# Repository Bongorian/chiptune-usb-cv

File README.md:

# Chiptune USB/CV

SAA1099 × 1、SN76489AN × 2、RP2040を搭載したPSG音源のハードウェア・ファームウェアプロジェクトです。
USB MIDI、TRS MIDI、2系統のCV／ゲート入力と、OLED・3ボタンによる操作を想定しています。
回路図、配線済みPCB、JLCPCB向け製造データ、設計資料を収録しています。

ファームウェアはv0.11.0-alphaです。初期配置はMIDI 10（ch1–6: SAA、ch7–9: 左右SNトーン、ch10: 左右SNノイズ）。DIRECT/POLY演奏、PAN/CC10、音色編集、Patch/Track/Project/System保存に対応します。[操作資料](firmware/README.md)と[音源構成](firmware/SOUND_DESIGN.md)を参照してください。

SN共通クロックはHz／PIO値で設定でき、RAW／BASE／FULL、2スロットFX、計算周波数と転送待ちの診断に対応します。[クロック仕様と実機未確認事項](firmware/SN_CLOCK.md)を参照してください。

保存形式はversion 11、Web MIDI通信はprotocol 3/schema 11です。旧形式の音色・CV校正・明るさは移行しません。起動時のフラッシュ消去・書き込みは行いません。

自動テスト・ARMビルド・UF2検証の結果は[検証記録](firmware/dist/Test_Verification.json)に記録しています。実機の音声出力、電気特性、1 ms更新の最悪実行時間は未検証です。[検証範囲](firmware/ARCHITECTURE.md)と[実機確認項目](firmware/BRINGUP.md)を参照してください。

[**Wave Lab — Web MIDI音色エディタ**](https://bongorian.github.io/chiptune-usb-cv/)

Wave Labのソースは`editor/`にあります。公開版のほか、ローカルHTTPサーバーでも実行できます。[音作り](firmware/SOUND_DESIGN.md)と[エディタの使い方](editor/README.md)を参照してください。

## 仕様

| 項目 | 内容 |
|---|---|
| 基板 | 85 × 54 mm、4層、FR-4 1.6 mm、角R3、M2用取り付け穴 |
| マイコン | RP2040、外部QSPIフラッシュ |
| 音源 | SAA1099 DIP18 × 1、SN76489AN DIP16 × 2 |
| 電源 | USB-C給電 |
| MIDI | USB MIDIデバイス、3.5 mm TRS Type A入力 |
| CV | 1 V/oct入力 × 2、系統別の2点校正を想定 |
| ゲート | 0–5 V／0–10 V入力 × 2 |
| オーディオ | 3.5 mmステレオライン出力、入力インピーダンス10 kΩ以上の外部アンプ向け |
| 操作 | 0.96インチ128 × 64 OLED、3ボタン |

## リポジトリ構成

| ディレクトリ | 内容 |
|---|---|
| `routed/` | 配線済みKiCadプロジェクト、シンボル、フットプリント |
| `hardware/` | 回路・配置生成用の未配線プロジェクト |
| `editor/` | GitHub Pages向けWeb MIDI音色エディタ、波形・ADSR・16ステップ・クロック・CV設定 |
| `firmware/` | RP2040音源エンジン、USB／TRS MIDI、CV／ゲート、OLED UI、プリセット、UF2 |
| `mechanical/` | 3Dプリント用ケース、STL・STEP、寸法図・組み立て手順 |
| `docs/` | 回路仕様、操作設計、配線ルール |
| `scripts/` | 設計生成、配置、配線、検証、製造データ出力用スクリプト |
| `outputs/jlc-one/` | JLCPCB向け提出ファイルと組み立て資料 |
| `outputs/assembly-review/` | 実装座標・ピン1・極性の照合資料 |
| `outputs/review/` | 基板図とUIモックアップ |
| `research/` | 部品カタログ属性と実装ライブラリ参照図 |
| `variants/` | 設計比較用の基板データ |

## KiCadで開く

[`routed/Chiptune_USB_CV.kicad_pro`](routed/Chiptune_USB_CV.kicad_pro) を開いてください。
製造用のPCBは同じディレクトリの `Chiptune_USB_CV.kicad_pcb` です。

KiCad 9.0.9で作成しています。シンボルとフットプリントは同梱し、`${KIPRJMOD}`から参照します。
一部の3DモデルにはKiCad標準ライブラリが必要です。

## 製造データ

[`outputs/jlc-one/upload/`](outputs/jlc-one/upload/) にJLCPCB／JLCONE向けの提出ファイルがあります。

| ファイル | 用途 |
|---|---|
| [`Chiptune_Gerber.zip`](outputs/jlc-one/upload/Chiptune_Gerber.zip) | 基板製造データ |
| [`Chiptune_BOM.csv`](outputs/jlc-one/upload/Chiptune_BOM.csv) | 部品表・LCSC部品番号 |
| [`Chiptune_CPL.csv`](outputs/jlc-one/upload/Chiptune_CPL.csv) | 表面実装座標・回転角 |

Gerber ZIP、BOM、CPLをそれぞれ対応する欄へ指定します。
[製造資料一式のZIP](outputs/Chiptune_JLC_ONE_Public.zip) は展開し、内部の提出ファイルを使用してください。

表面実装対象は141点、BOMは41行・40品種です。
音源ICとDIPソケット、OLEDモジュール、任意のSWDヘッダーは手実装します。
組み立て手順と製造条件は [`outputs/jlc-one/README.txt`](outputs/jlc-one/README.txt) を参照してください。
発注時は部品在庫と実装プレビューのピン1・極性・向きを確認してください。

## 3Dプリント用ケース

[ケースの設計・印刷・組み立て資料](mechanical/README.md)にSTL、STEP、寸法図を収録しています。
印刷用データは[ケースZIP](mechanical/exports/Chiptune_Enclosure_3DPrint.zip)から取得できます。
上下2分割、底面のM2インサート固定、音源ICとOLEDの開口、3ボタンの押し子を備えます。
ケース本体は89.8 × 58.8 × 23.0 mmです。OLEDは別モジュールを基板上の5 mmスペーサーで取り付けます。

## ファームウェア

[ファームウェアの操作資料](firmware/README.md)と[配布UF2](firmware/dist/chiptune-v0.11.0-alpha.uf2)を収録しています。
発音表示はSQUARE 50%（SAA/SN）、PULSE 約6.7%（SN Periodic Noise＋Tone 3）、ENV WAVE（SAA）、TONE + NOISE（SAA）を区別します。選択した発音で使える設定を表示します。

本体の3ボタンで、SAAのENV発振・ソフトADSR、SNのステレオ音色・実クロック変調、MIDI/CV/Gateの割り当て、パターン編集と保存を操作できます。
[Androidからの更新手順](firmware/ANDROID_UPDATE.md)、[実機確認項目](firmware/BRINGUP.md)、[検証記録](firmware/dist/Verification.json)も参照してください。
−と＋を押しながらUSBを接続するか、SYSTEM > USB UPDATEからROMブートローダーへ入れます。

## 開発状況

- 基板検査: DRC 0、未接続0、回路図との一致問題0、ERC 0。
- 設計照合: 152フットプリントの配置・端子接続と、音源バスの768ケースを検査済み。
- ファームウェア: v0.11.0-alpha。Track/Patch/Voice/物理回路を分離した単一エンジン。DIRECT/POLY、SAA ENV/AMとSNレイヤー、独立Patch/Track/Project/System保存、Wave Lab protocol 3。ホスト・ARM・Web試験とUF2検証は[検証記録](firmware/dist/Test_Verification.json)を参照。実機評価は未完了。
- 実機検証: 電源電流・突入電流、音声出力、CV校正、取り付け公差の評価は未完了。

[OLEDの描画例](firmware/assets/ui-v10.png)は、実装したCの描画処理から生成しています。

## 検証コマンド

Ubuntu上のKiCad CLIと、`pcbnew`を利用できるPython環境を使用します。
画像出力にはCairoSVGが必要です。

```bash
kicad-cli pcb drc --format json --schematic-parity --exit-code-violations \
  -o outputs/drc-routed.json routed/Chiptune_USB_CV.kicad_pcb
kicad-cli sch erc --format json --exit-code-violations \
  -o outputs/erc-routing.json routed/Chiptune_USB_CV.kicad_sch
/usr/bin/python3 scripts/check_routing.py
/usr/bin/python3 scripts/check_bus_encoding.py
```

検証レポートは `outputs/`、製造パッケージの検査結果は `outputs/jlc-one/checks/` にあります。
配置・配線の再生成スクリプトはKiCadファイルを書き換えるため、設計変更用のブランチで実行してください。

## 設計資料

- [基板説明資料（日本語・9ページPDF）](output/pdf/Chiptune_USB_CV_Guide_JA.pdf)
- [回路仕様・操作設計](docs/USB-CV-design-notes.txt)
- [配線方針・線幅](docs/routing-notes.txt)
- [実装ライブラリの照合記録](outputs/assembly-review/Assembly_Review.txt)
- [ピン1・極性の参照図](outputs/assembly-review/Placement_Pin1.png)
- [部品ライブラリ・資料の出典](THIRD_PARTY_NOTICES.md)

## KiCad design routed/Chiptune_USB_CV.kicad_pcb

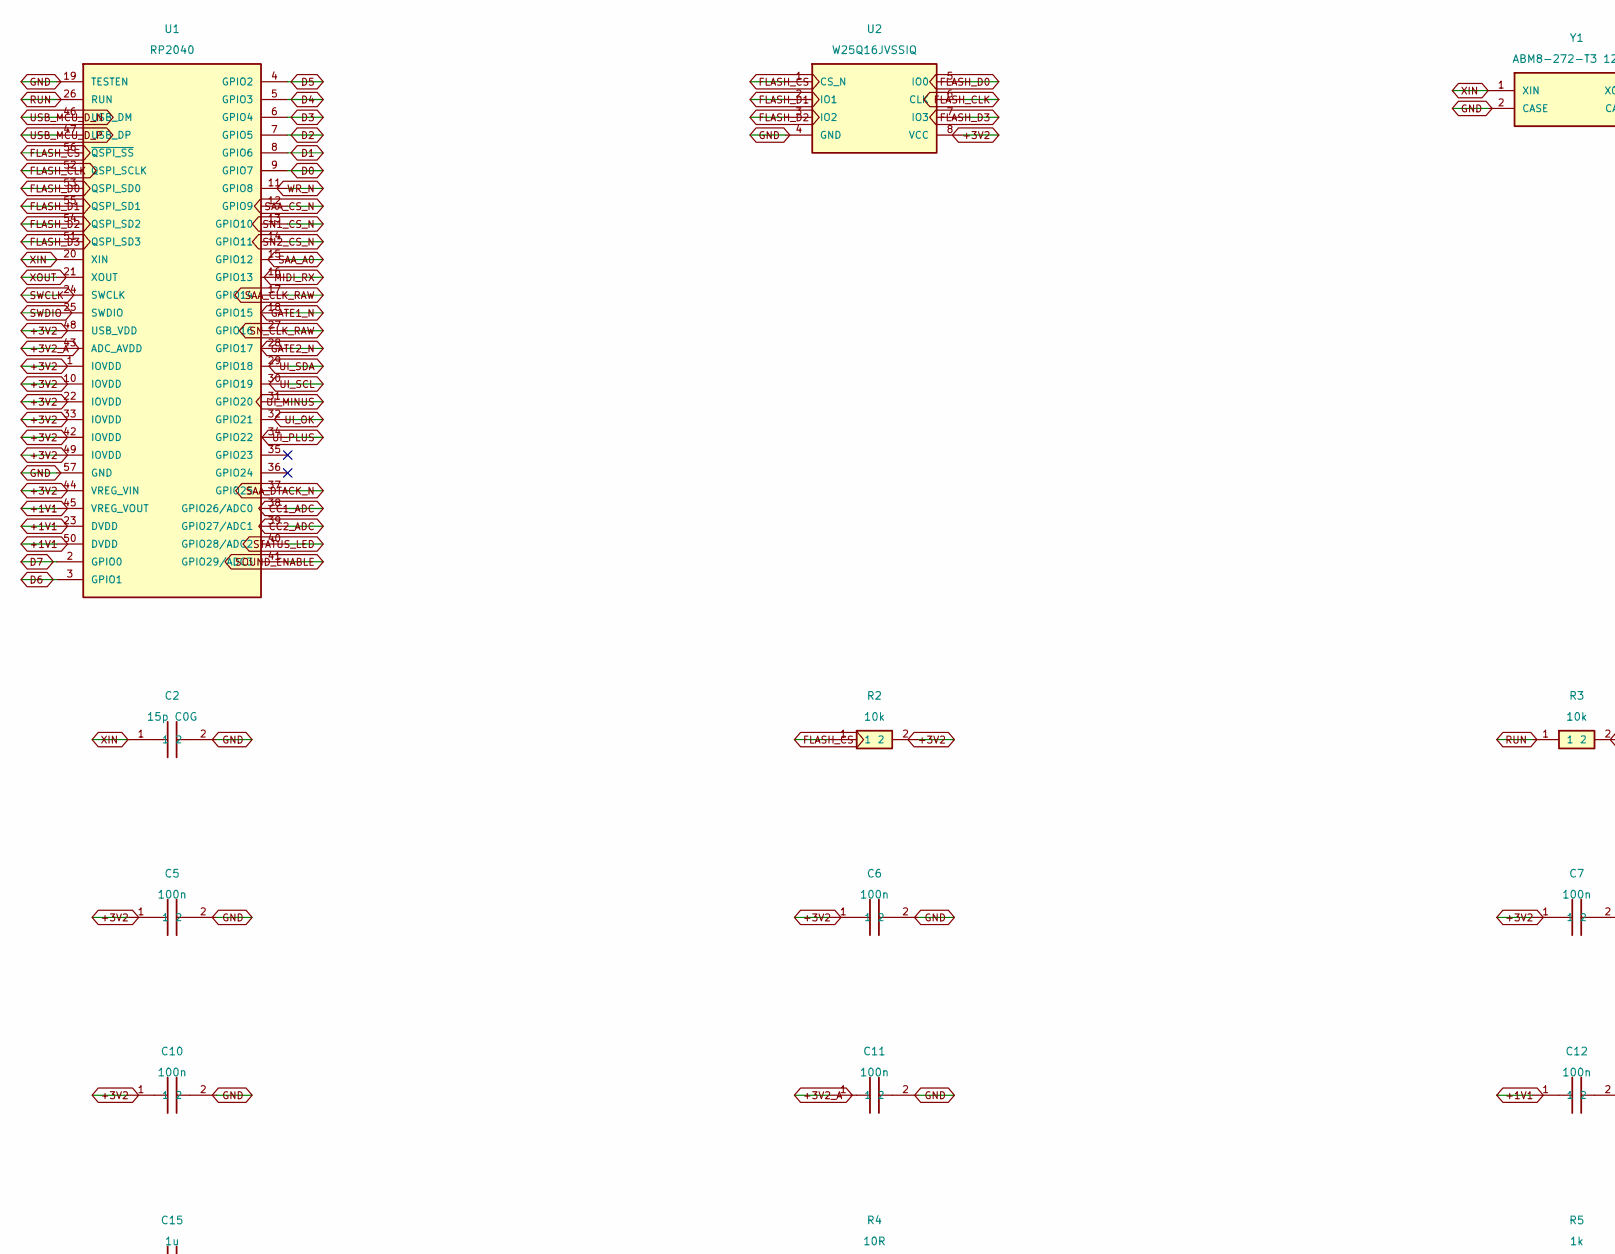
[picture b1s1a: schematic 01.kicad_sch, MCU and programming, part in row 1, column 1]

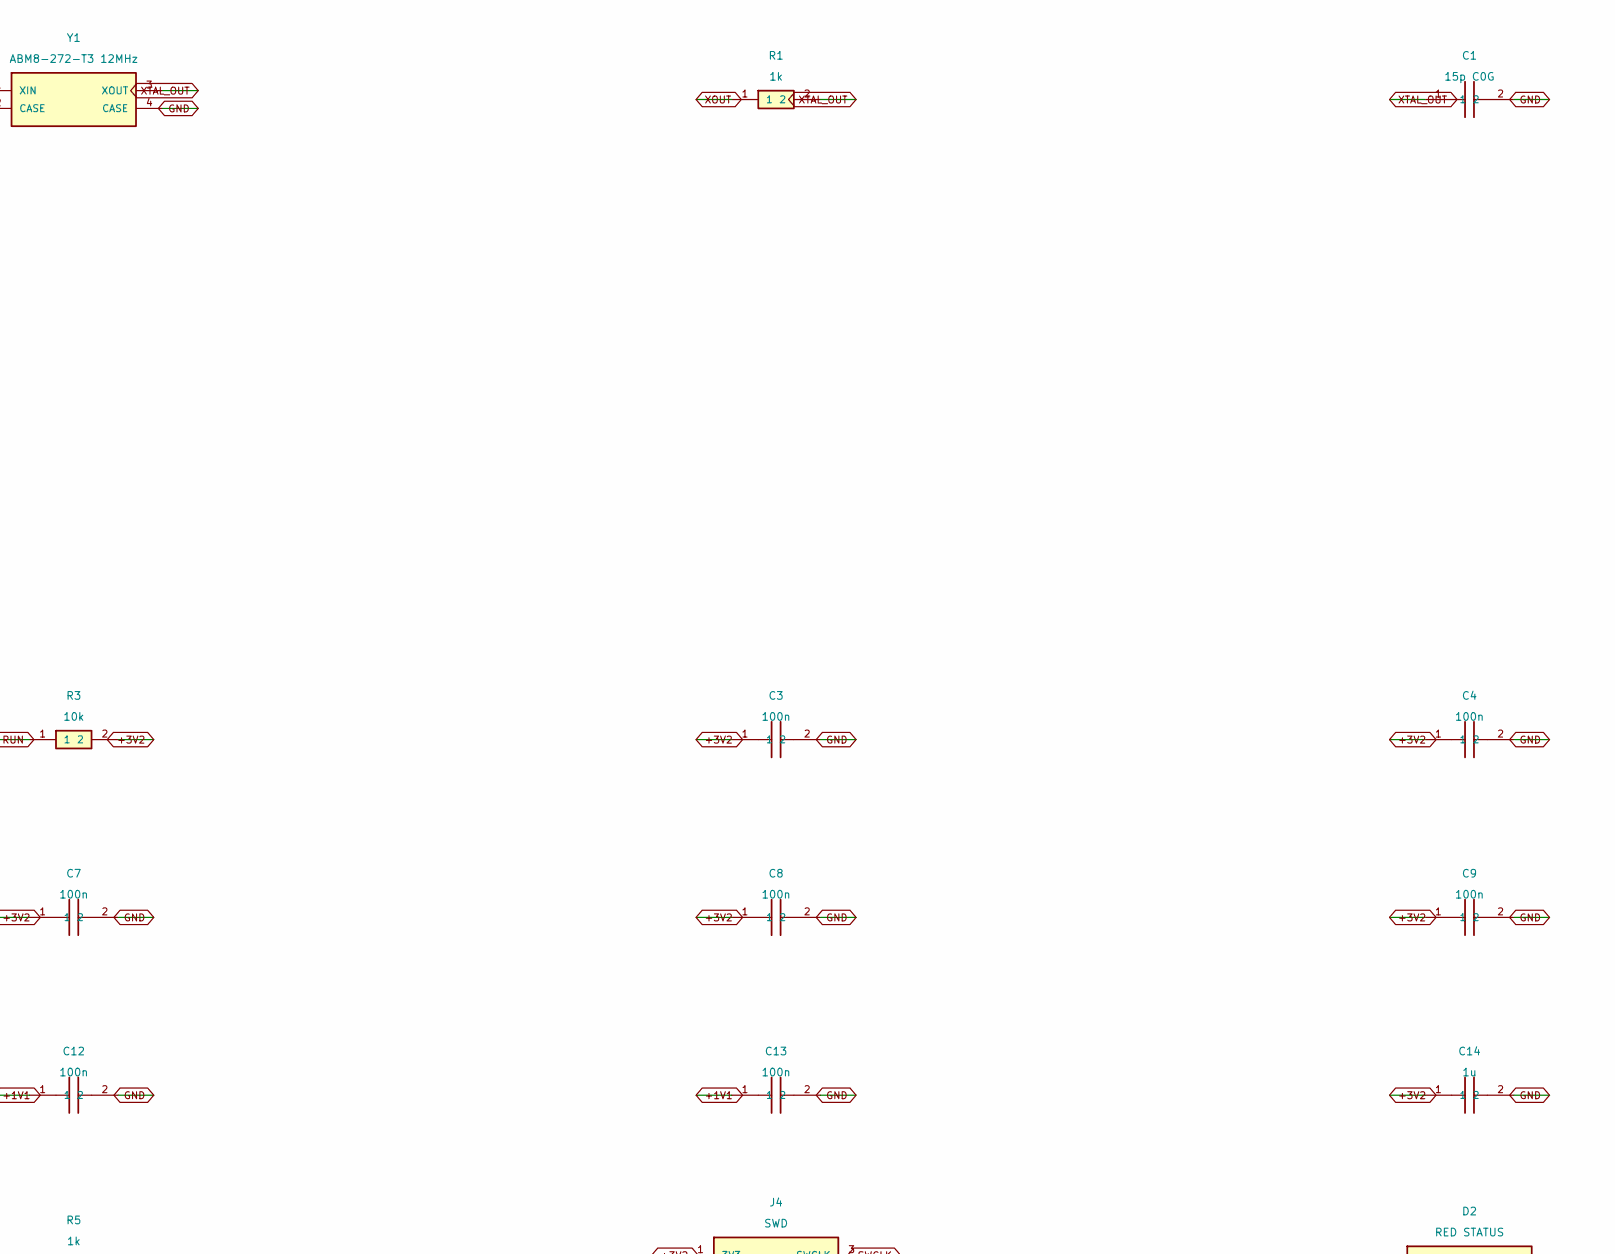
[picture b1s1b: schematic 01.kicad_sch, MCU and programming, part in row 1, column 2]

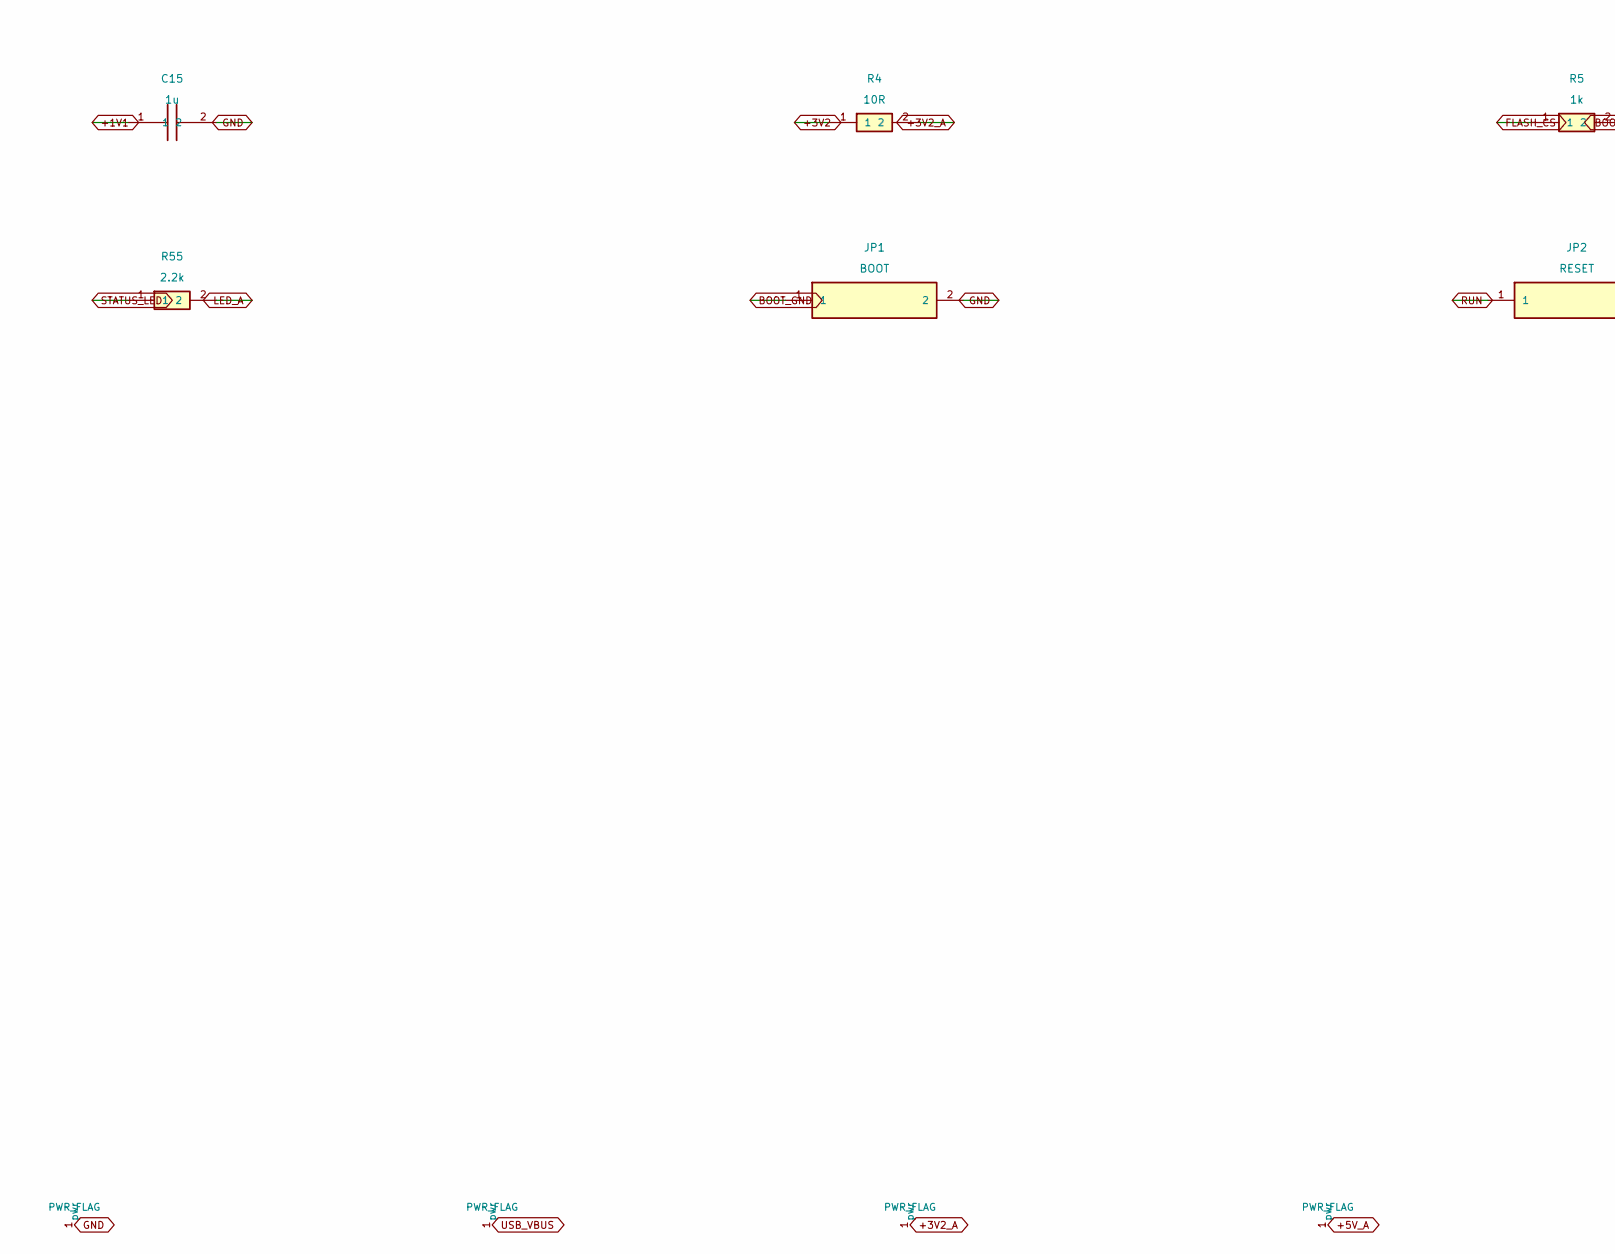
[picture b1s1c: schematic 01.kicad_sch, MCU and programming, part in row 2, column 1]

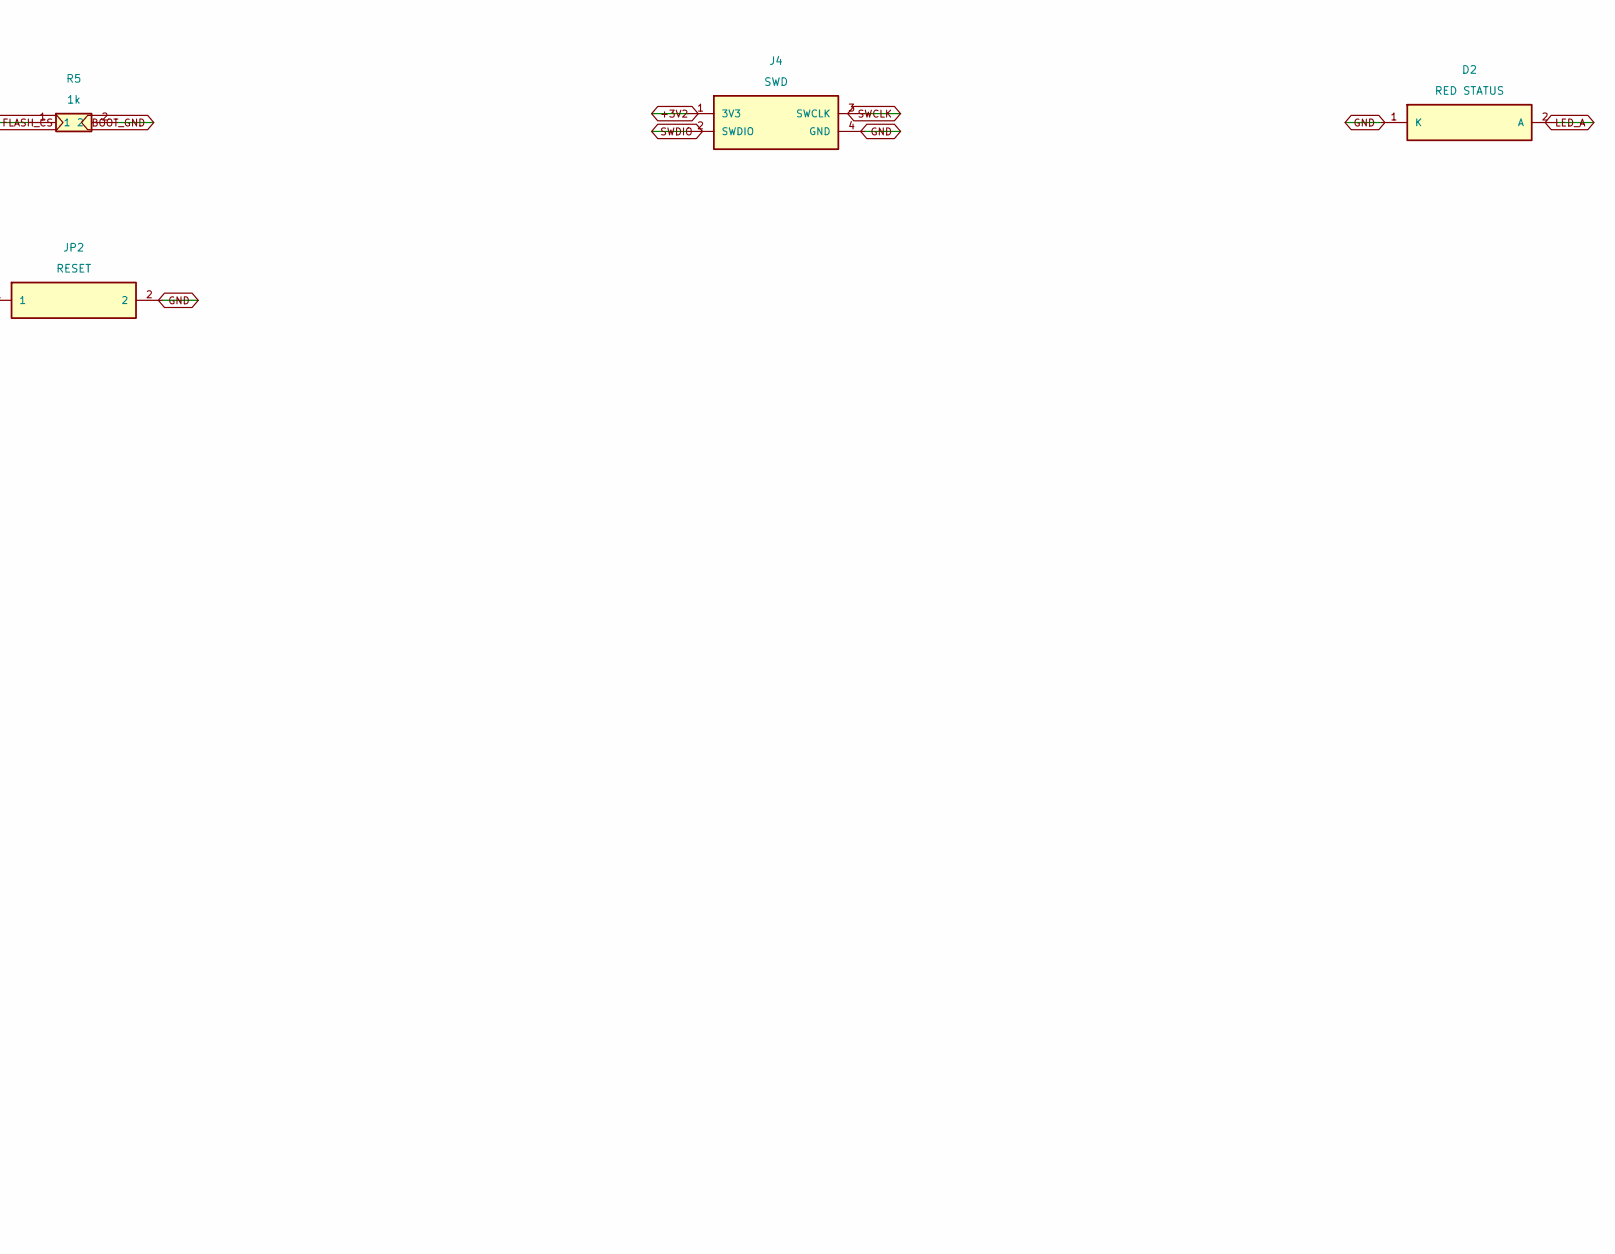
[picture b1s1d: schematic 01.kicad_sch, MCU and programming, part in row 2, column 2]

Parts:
C1: 15p C0G; Board_C1; LCSC C1644
C2: 15p C0G; Board_C2; LCSC C1644
C3: 100n; Board_C3; LCSC C14663
C4: 100n; Board_C4; LCSC C14663
C5: 100n; Board_C5; LCSC C14663
C6: 100n; Board_C6; LCSC C14663
C7: 100n; Board_C7; LCSC C14663
C8: 100n; Board_C8; LCSC C14663
C9: 100n; Board_C9; LCSC C14663
C10: 100n; Board_C10; LCSC C14663
C11: 100n; Board_C11; LCSC C14663
C12: 100n; Board_C12; LCSC C14663
C13: 100n; Board_C13; LCSC C14663
C14: 1u; Board_C14; LCSC C15849
C15: 1u; Board_C15; LCSC C15849
D2: RED STATUS; Board_D2; LCSC C2286
J4: SWD; Board_J4
JP1: BOOT; Board_JP1
JP2: RESET; Board_JP2
R1: 1k; Board_R1; LCSC C21190
R2: 10k; Board_R2; LCSC C25804
R3: 10k; Board_R3; LCSC C25804
R4: 10R; Board_R4; LCSC C22859
R5: 1k; Board_R5; LCSC C21190
R55: 2.2k; Board_R55; LCSC C4190
U1: RP2040; Board_U1; LCSC C2040
U2: W25Q16JVSSIQ; Board_U2; LCSC C131025
Y1: ABM8-272-T3 12MHz; Board_Y1; LCSC C20625731

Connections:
+1V1: C12.1, C13.1, C15.1, U1.23 (DVDD), U1.45 (VREG_VOUT), U1.50 (DVDD)
+3V2: C3.1, C4.1, C5.1, C6.1, C7.1, C8.1, C9.1, C10.1, C14.1, J4.1 (3V3), R2.2, R3.2, R4.1, U1.1 (IOVDD), U1.10 (IOVDD), U1.22 (IOVDD), U1.33 (IOVDD), U1.42 (IOVDD), U1.44 (VREG_VIN), U1.48 (USB_VDD), U1.49 (IOVDD), U2.8 (VCC); also elsewhere on the board
+3V2_A: C11.1, R4.2, U1.43 (ADC_AVDD)
BOOT_GND: JP1.1, R5.2
CC1_ADC: U1.38 (GPIO26/ADC0); also elsewhere on the board
CC2_ADC: U1.39 (GPIO27/ADC1); also elsewhere on the board
D0: U1.9 (GPIO7); also elsewhere on the board
D1: U1.8 (GPIO6); also elsewhere on the board
D2: U1.7 (GPIO5); also elsewhere on the board
D3: U1.6 (GPIO4); also elsewhere on the board
D4: U1.5 (GPIO3); also elsewhere on the board
D5: U1.4 (GPIO2); also elsewhere on the board
D6: U1.3 (GPIO1); also elsewhere on the board
D7: U1.2 (GPIO0); also elsewhere on the board
FLASH_CLK: U1.52 (QSPI_SCLK), U2.6 (CLK)
FLASH_CS: R2.1, R5.1, U1.56 (~QSPI_SS), U2.1 (CS_N)
FLASH_D0: U1.53 (QSPI_SD0), U2.5 (IO0)
FLASH_D1: U1.55 (QSPI_SD1), U2.2 (IO1)
FLASH_D2: U1.54 (QSPI_SD2), U2.3 (IO2)
FLASH_D3: U1.51 (QSPI_SD3), U2.7 (IO3)
GATE1_N: U1.18 (GPIO15); also elsewhere on the board
GATE2_N: U1.28 (GPIO17); also elsewhere on the board
GND: C1.2, C2.2, C3.2, C4.2, C5.2, C6.2, C7.2, C8.2, C9.2, C10.2, C11.2, C12.2, C13.2, C14.2, C15.2, D2.1 (K), J4.4 (GND), JP1.2, JP2.2, U1.19 (TESTEN), U1.57 (GND), U2.4 (GND), Y1.2 (CASE), Y1.4 (CASE); also elsewhere on the board
LED_A: D2.2 (A), R55.2
MIDI_RX: U1.16 (GPIO13); also elsewhere on the board
RUN: JP2.1, R3.1, U1.26 (RUN)
SAA_A0: U1.15 (GPIO12); also elsewhere on the board
SAA_CLK_RAW: U1.17 (GPIO14); also elsewhere on the board
SAA_CS_N: U1.12 (GPIO9); also elsewhere on the board
SAA_DTACK_N: U1.37 (GPIO25); also elsewhere on the board
SN1_CS_N: U1.13 (GPIO10); also elsewhere on the board
SN2_CS_N: U1.14 (GPIO11); also elsewhere on the board
SN_CLK_RAW: U1.27 (GPIO16); also elsewhere on the board
SOUND_ENABLE: U1.41 (GPIO29/ADC3); also elsewhere on the board
STATUS_LED: R55.1, U1.40 (GPIO28/ADC2)
SWCLK: J4.3 (SWCLK), U1.24 (SWCLK)
SWDIO: J4.2 (SWDIO), U1.25 (SWDIO)
UI_MINUS: U1.31 (GPIO20); also elsewhere on the board
UI_OK: U1.32 (GPIO21); also elsewhere on the board
UI_PLUS: U1.34 (GPIO22); also elsewhere on the board
UI_SCL: U1.30 (GPIO19); also elsewhere on the board
UI_SDA: U1.29 (GPIO18); also elsewhere on the board
USB_MCU_D_N: U1.46 (USB_DM); also elsewhere on the board
USB_MCU_D_P: U1.47 (USB_DP); also elsewhere on the board
WR_N: U1.11 (GPIO8); also elsewhere on the board
XIN: C2.1, U1.20 (XIN), Y1.1 (XIN)
XOUT: R1.1, U1.21 (XOUT)
XTAL_OUT: C1.1, R1.2, Y1.3 (XOUT)

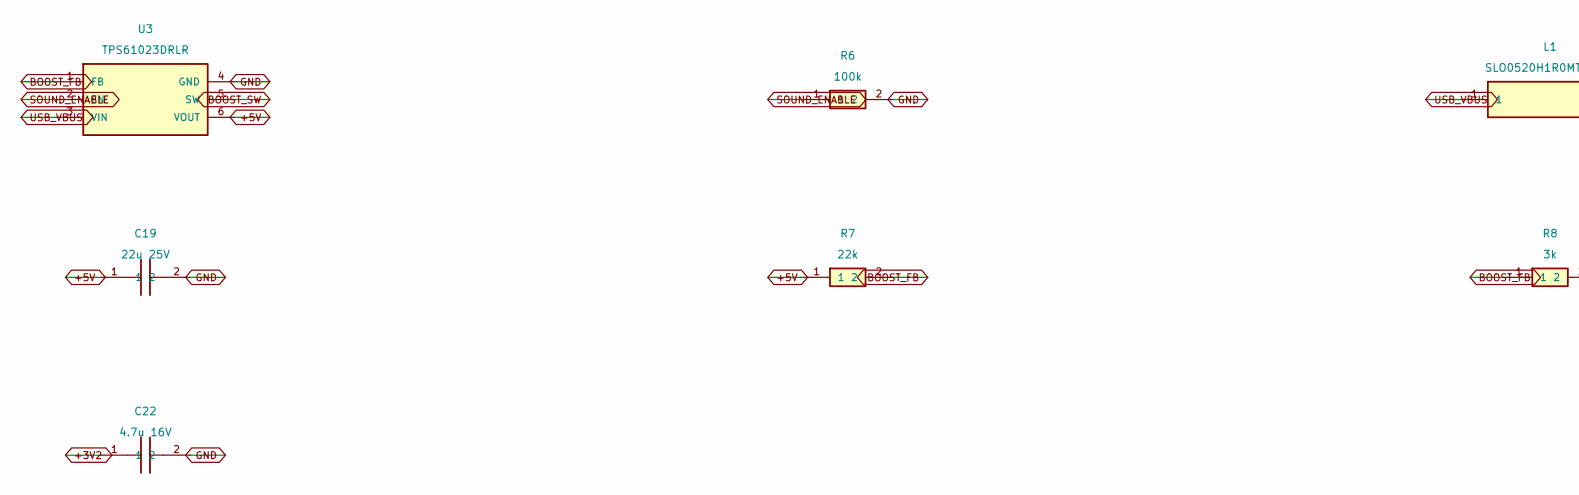
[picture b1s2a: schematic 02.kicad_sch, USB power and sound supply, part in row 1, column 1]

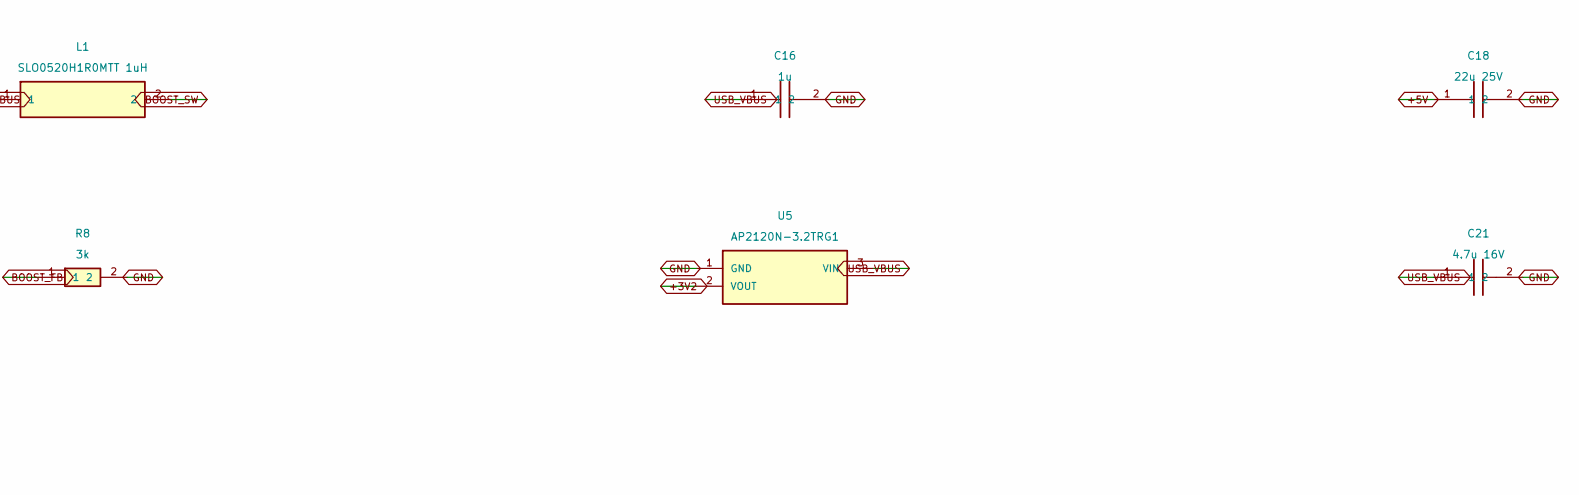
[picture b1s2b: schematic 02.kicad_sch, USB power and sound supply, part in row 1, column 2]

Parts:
C16: 1u; Board_C16; LCSC C15849
C18: 22u 25V; Board_C18; LCSC C45783
C19: 22u 25V; Board_C19; LCSC C45783
C21: 4.7u 16V; Board_C21; LCSC C19666
C22: 4.7u 16V; Board_C22; LCSC C19666
L1: SLO0520H1R0MTT 1uH; Board_L1; LCSC C325980
R6: 100k; Board_R6; LCSC C25803
R7: 22k; Board_R7; LCSC C31850
R8: 3k; Board_R8; LCSC C4211
U3: TPS61023DRLR; Board_U3; LCSC C919459
U5: AP2120N-3.2TRG1; Board_U5; LCSC C6500828

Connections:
+3V2: C22.1, U5.2 (VOUT); also elsewhere on the board
+5V: C18.1, C19.1, R7.1, U3.6 (VOUT); also elsewhere on the board
BOOST_FB: R7.2, R8.1, U3.1 (FB)
BOOST_SW: L1.2, U3.5 (SW)
GND: C16.2, C18.2, C19.2, C21.2, C22.2, R6.2, R8.2, U3.4 (GND), U5.1 (GND); also elsewhere on the board
SOUND_ENABLE: R6.1, U3.2 (EN); also elsewhere on the board
USB_VBUS: C16.1, C21.1, L1.1, U3.3 (VIN), U5.3 (VIN); also elsewhere on the board

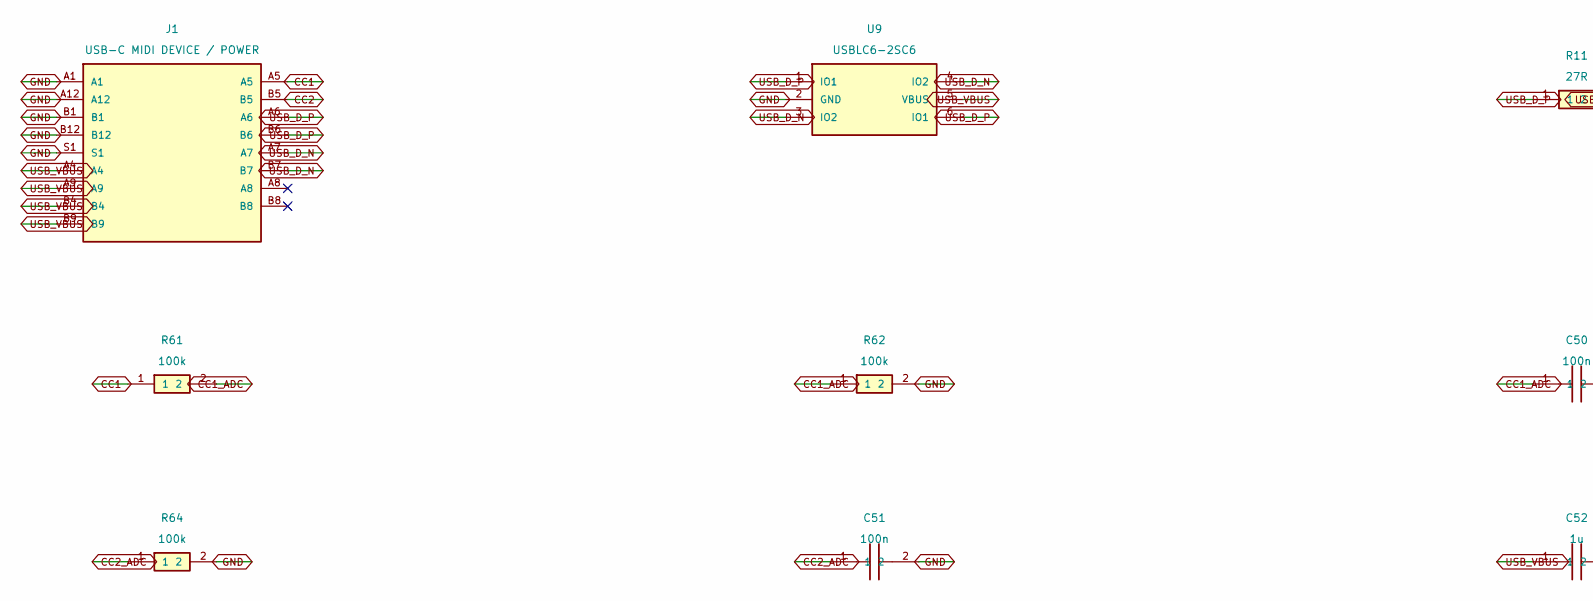
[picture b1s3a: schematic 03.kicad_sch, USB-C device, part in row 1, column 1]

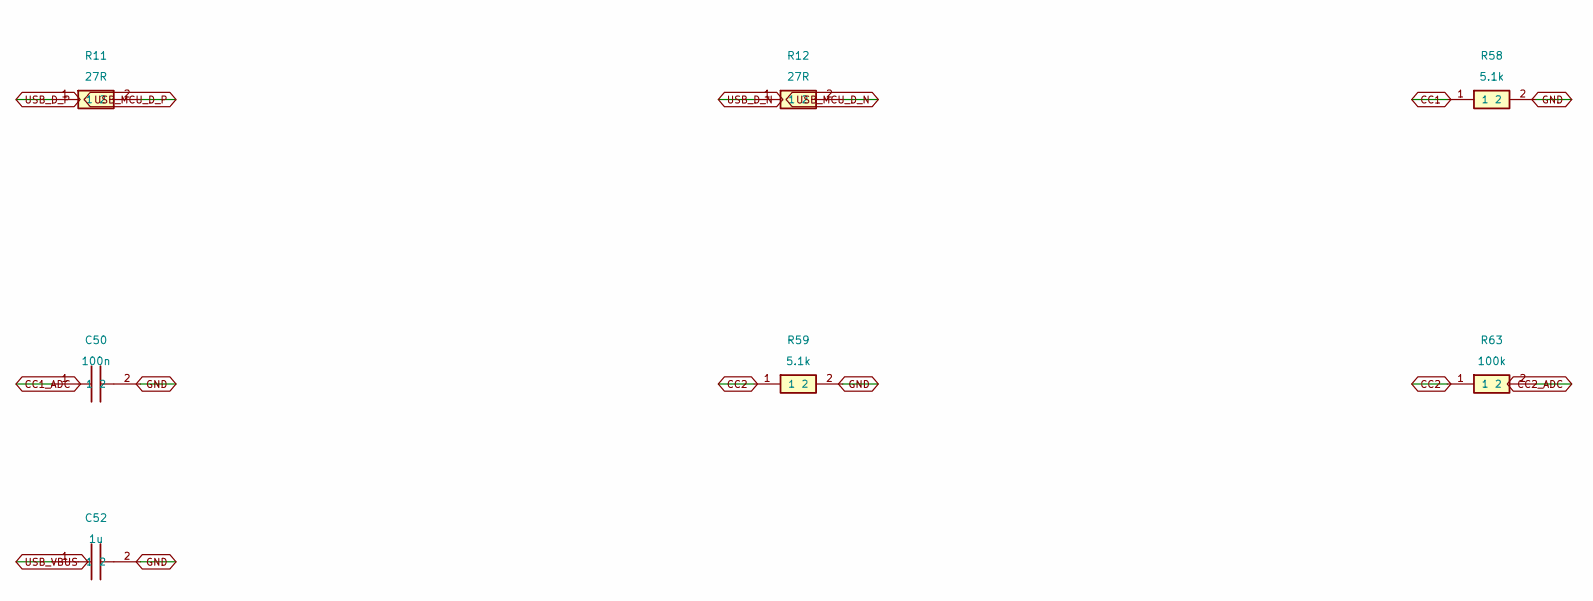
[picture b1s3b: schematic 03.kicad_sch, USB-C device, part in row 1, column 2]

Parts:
C50: 100n; Board_C50; LCSC C14663
C51: 100n; Board_C51; LCSC C14663
C52: 1u; Board_C52; LCSC C15849
J1: USB-C MIDI DEVICE / POWER; Board_J1; LCSC C165948
R11: 27R; Board_R11; LCSC C25190
R12: 27R; Board_R12; LCSC C25190
R58: 5.1k; Board_R58; LCSC C23186
R59: 5.1k; Board_R59; LCSC C23186
R61: 100k; Board_R61; LCSC C25803
R62: 100k; Board_R62; LCSC C25803
R63: 100k; Board_R63; LCSC C25803
R64: 100k; Board_R64; LCSC C25803
U9: USBLC6-2SC6; Board_U9; LCSC C7519

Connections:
CC1: J1.A5, R58.1, R61.1
CC1_ADC: C50.1, R61.2, R62.1; also elsewhere on the board
CC2: J1.B5, R59.1, R63.1
CC2_ADC: C51.1, R63.2, R64.1; also elsewhere on the board
GND: C50.2, C51.2, C52.2, J1.A1, J1.A12, J1.B1, J1.B12, J1.S1, R58.2, R59.2, R62.2, R64.2, U9.2 (GND); also elsewhere on the board
USB_D_N: J1.A7, J1.B7, R12.1, U9.3 (IO2), U9.4 (IO2)
USB_D_P: J1.A6, J1.B6, R11.1, U9.1 (IO1), U9.6 (IO1)
USB_MCU_D_N: R12.2; also elsewhere on the board
USB_MCU_D_P: R11.2; also elsewhere on the board
USB_VBUS: C52.1, J1.A4, J1.A9, J1.B4, J1.B9, U9.5 (VBUS); also elsewhere on the board

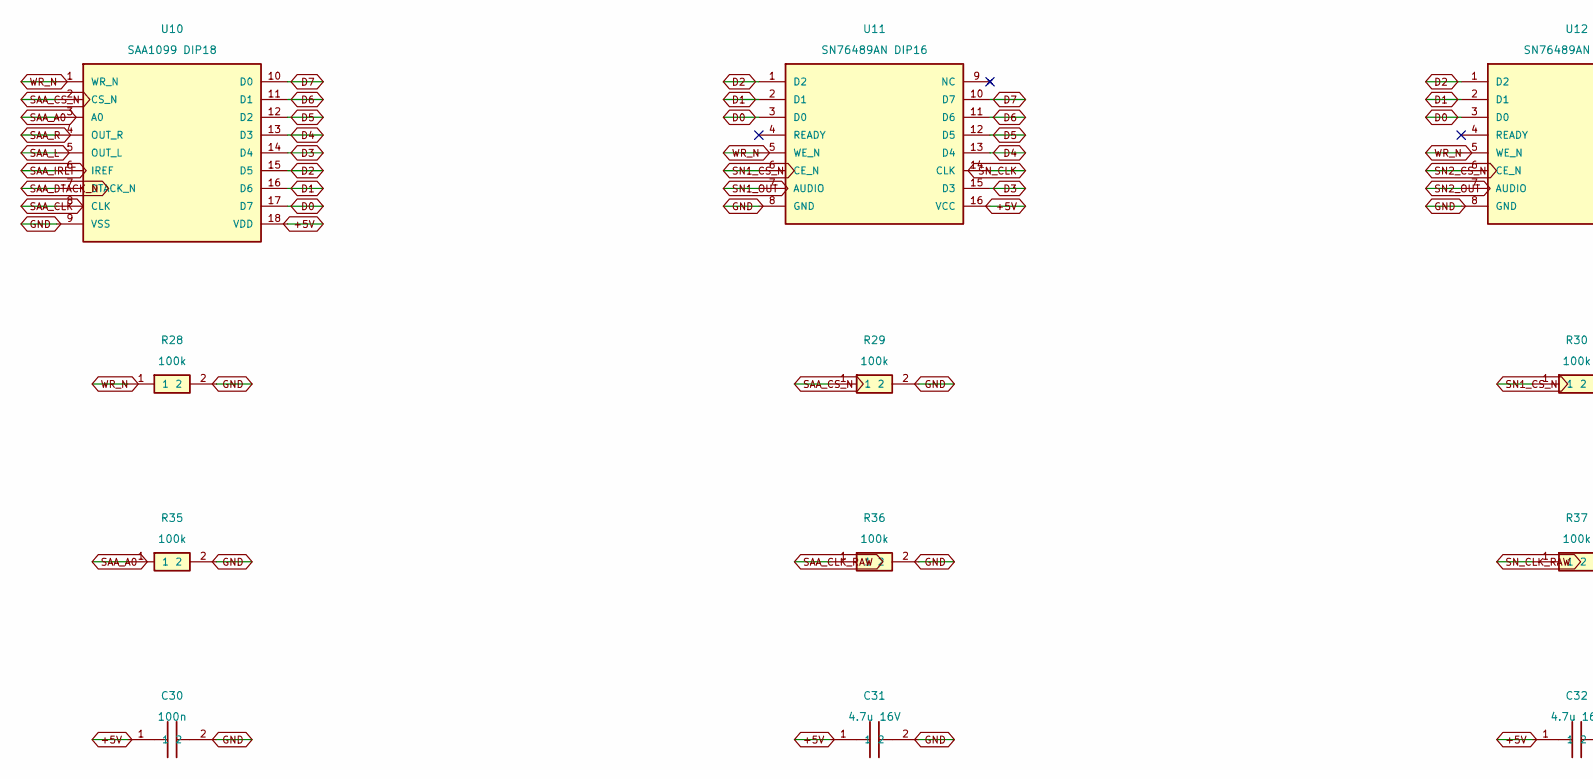
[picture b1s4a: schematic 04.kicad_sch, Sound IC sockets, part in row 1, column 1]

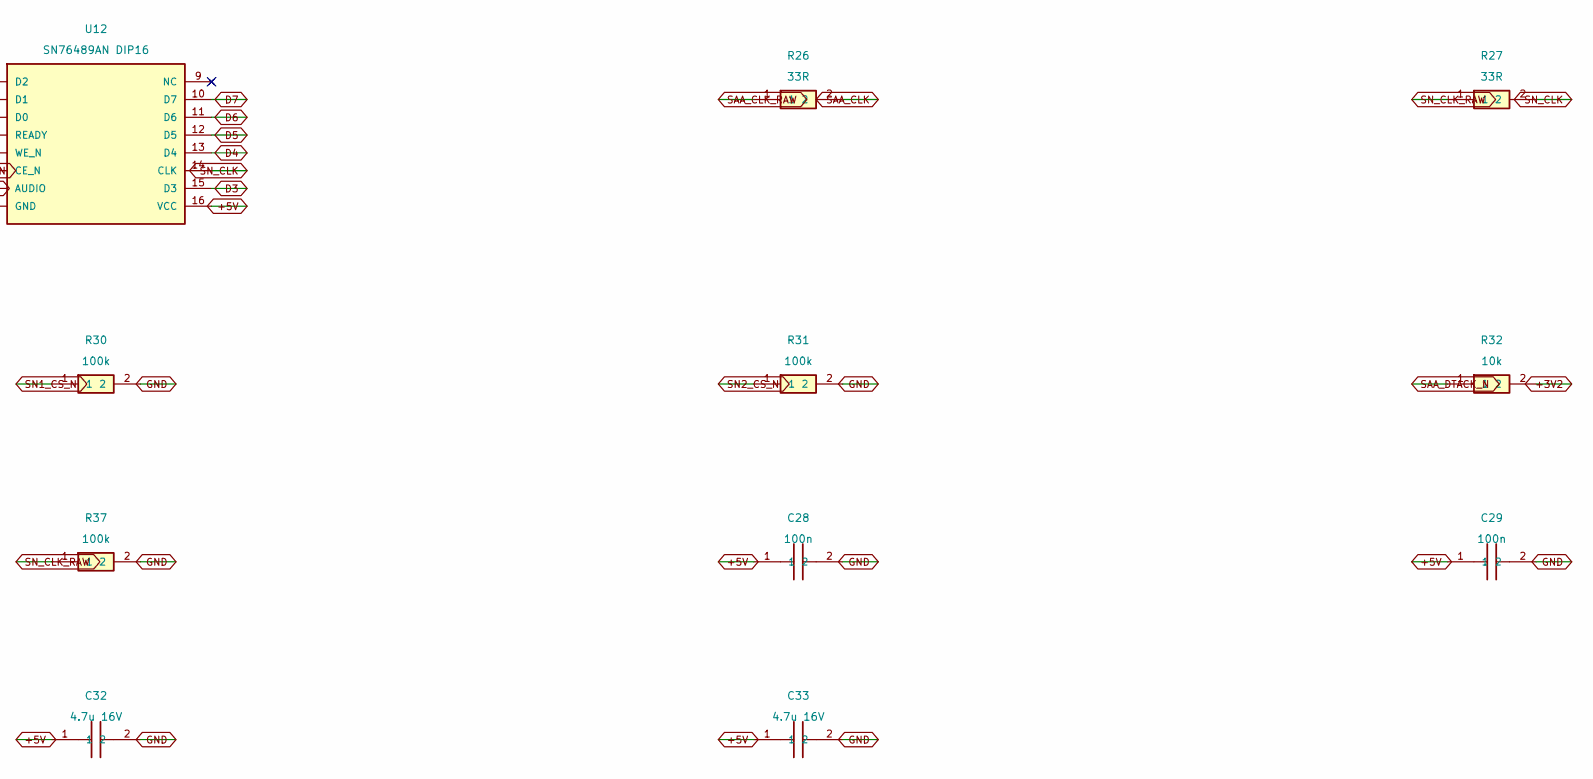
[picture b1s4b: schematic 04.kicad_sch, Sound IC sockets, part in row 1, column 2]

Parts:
C28: 100n; Board_C28; LCSC C14663
C29: 100n; Board_C29; LCSC C14663
C30: 100n; Board_C30; LCSC C14663
C31: 4.7u 16V; Board_C31; LCSC C19666
C32: 4.7u 16V; Board_C32; LCSC C19666
C33: 4.7u 16V; Board_C33; LCSC C19666
R26: 33R; Board_R26; LCSC C23140
R27: 33R; Board_R27; LCSC C23140
R28: 100k; Board_R28; LCSC C25803
R29: 100k; Board_R29; LCSC C25803
R30: 100k; Board_R30; LCSC C25803
R31: 100k; Board_R31; LCSC C25803
R32: 10k; Board_R32; LCSC C25804
R35: 100k; Board_R35; LCSC C25803
R36: 100k; Board_R36; LCSC C25803
R37: 100k; Board_R37; LCSC C25803
U10: SAA1099 DIP18; Board_U10
U11: SN76489AN DIP16; Board_U11
U12: SN76489AN DIP16; Board_U12

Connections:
+3V2: R32.2; also elsewhere on the board
+5V: C28.1, C29.1, C30.1, C31.1, C32.1, C33.1, U10.18 (VDD), U11.16 (VCC), U12.16 (VCC); also elsewhere on the board
D0: U10.17 (D7), U11.3 (D0), U12.3 (D0); also elsewhere on the board
D1: U10.16 (D6), U11.2 (D1), U12.2 (D1); also elsewhere on the board
D2: U10.15 (D5), U11.1 (D2), U12.1 (D2); also elsewhere on the board
D3: U10.14 (D4), U11.15 (D3), U12.15 (D3); also elsewhere on the board
D4: U10.13 (D3), U11.13 (D4), U12.13 (D4); also elsewhere on the board
D5: U10.12 (D2), U11.12 (D5), U12.12 (D5); also elsewhere on the board
D6: U10.11 (D1), U11.11 (D6), U12.11 (D6); also elsewhere on the board
D7: U10.10 (D0), U11.10 (D7), U12.10 (D7); also elsewhere on the board
GND: C28.2, C29.2, C30.2, C31.2, C32.2, C33.2, R28.2, R29.2, R30.2, R31.2, R35.2, R36.2, R37.2, U10.9 (VSS), U11.8 (GND), U12.8 (GND); also elsewhere on the board
SAA_A0: R35.1, U10.3 (A0); also elsewhere on the board
SAA_CLK: R26.2, U10.8 (CLK)
SAA_CLK_RAW: R26.1, R36.1; also elsewhere on the board
SAA_CS_N: R29.1, U10.2 (CS_N); also elsewhere on the board
SAA_DTACK_N: R32.1, U10.7 (DTACK_N); also elsewhere on the board
SAA_IREF: U10.6 (IREF); also elsewhere on the board
SAA_L: U10.5 (OUT_L); also elsewhere on the board
SAA_R: U10.4 (OUT_R); also elsewhere on the board
SN1_CS_N: R30.1, U11.6 (CE_N); also elsewhere on the board
SN1_OUT: U11.7 (AUDIO); also elsewhere on the board
SN2_CS_N: R31.1, U12.6 (CE_N); also elsewhere on the board
SN2_OUT: U12.7 (AUDIO); also elsewhere on the board
SN_CLK: R27.2, U11.14 (CLK), U12.14 (CLK)
SN_CLK_RAW: R27.1, R37.1; also elsewhere on the board
WR_N: R28.1, U10.1 (WR_N), U11.5 (WE_N), U12.5 (WE_N); also elsewhere on the board

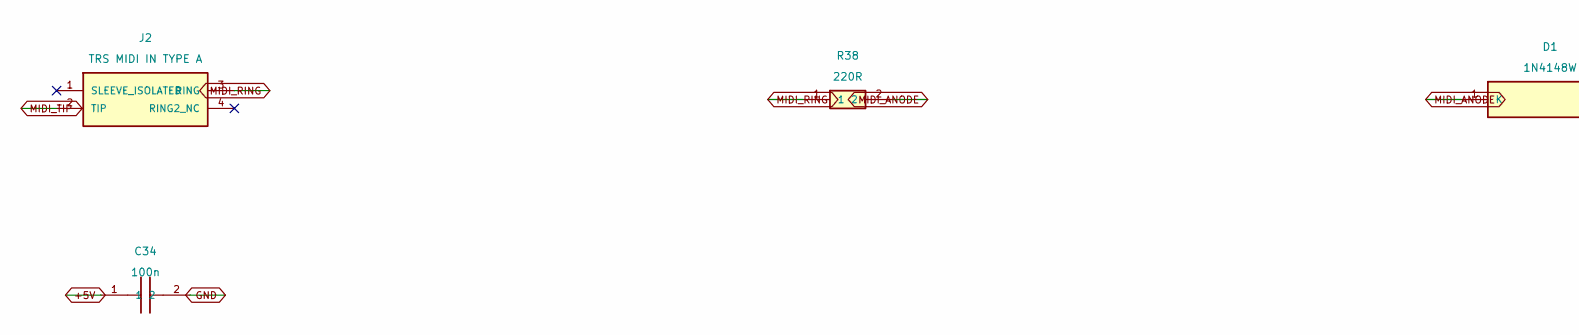
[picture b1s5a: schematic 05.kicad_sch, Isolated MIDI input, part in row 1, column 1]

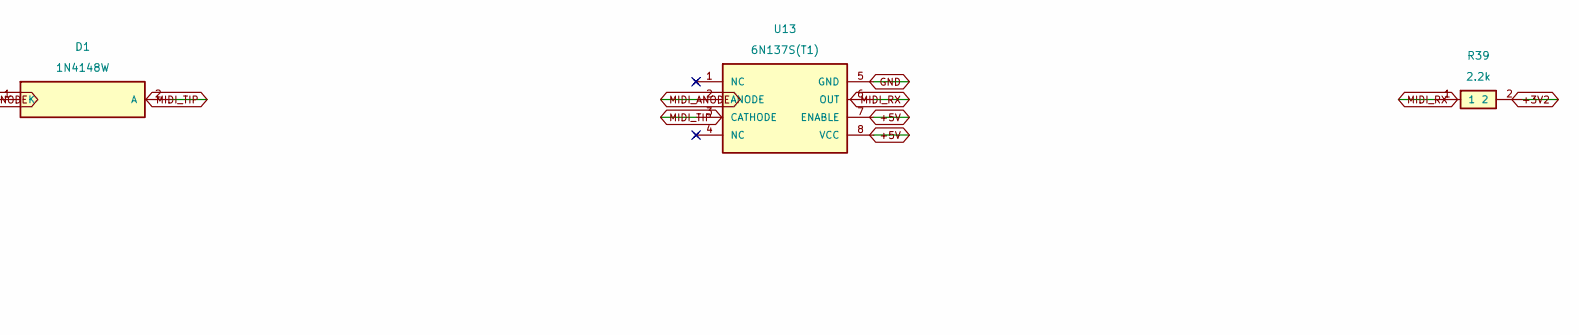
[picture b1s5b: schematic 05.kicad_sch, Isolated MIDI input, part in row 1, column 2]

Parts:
C34: 100n; Board_C34; LCSC C14663
D1: 1N4148W; Board_D1; LCSC C81598
J2: TRS MIDI IN TYPE A; Board_J2; LCSC C95562
R38: 220R; Board_R38; LCSC C22962
R39: 2.2k; Board_R39; LCSC C4190
U13: 6N137S(T1); Board_U13; LCSC C191867

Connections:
+3V2: R39.2; also elsewhere on the board
+5V: C34.1, U13.7 (ENABLE), U13.8 (VCC); also elsewhere on the board
GND: C34.2, U13.5 (GND); also elsewhere on the board
MIDI_ANODE: D1.1 (K), R38.2, U13.2 (ANODE)
MIDI_RING: J2.3 (RING), R38.1
MIDI_RX: R39.1, U13.6 (OUT); also elsewhere on the board
MIDI_TIP: D1.2 (A), J2.2 (TIP), U13.3 (CATHODE)
